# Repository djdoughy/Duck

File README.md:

# Duck
Pseudo Sidechain Compressor
Based on Modular for the Masses "OK BOOMER" schematic

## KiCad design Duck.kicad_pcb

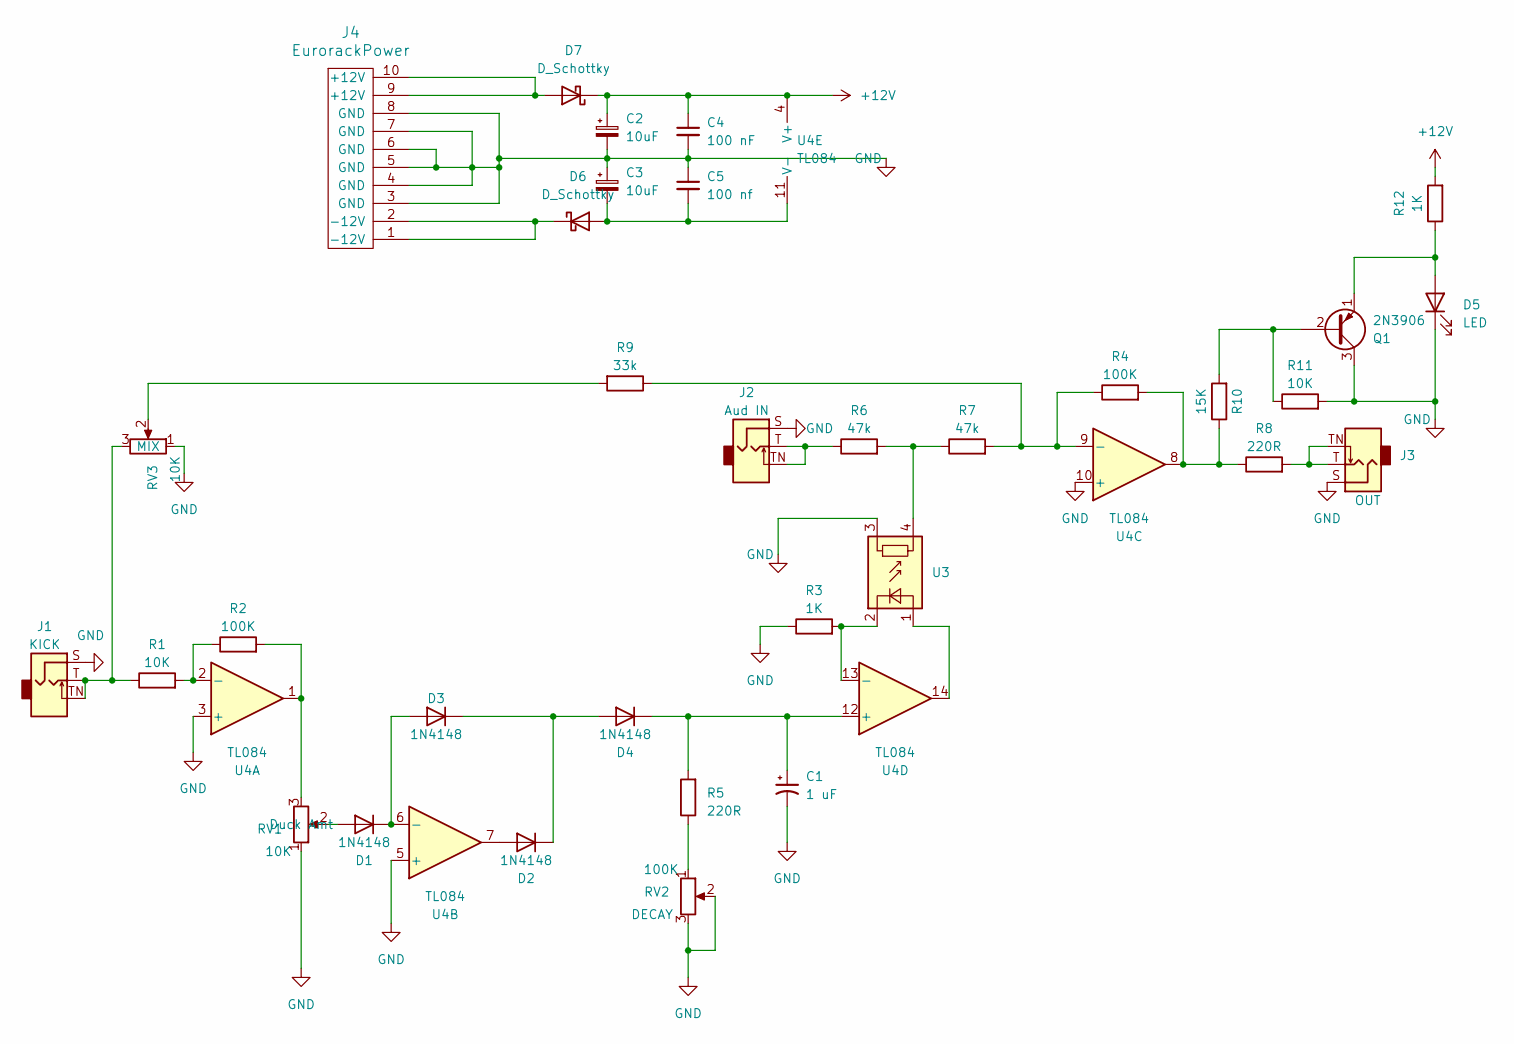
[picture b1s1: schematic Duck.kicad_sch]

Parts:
C1: 1 uF; CP_Radial_D5.0mm_P2.50mm
C2, C3: 10uF; CP_Radial_D5.0mm_P2.50mm
C4: 100 nF; C_Disc_D3.0mm_W2.0mm_P2.50mm
C5: 100 nf; C_Disc_D3.0mm_W2.0mm_P2.50mm
D1, D2, D3, D4: 1N4148; D_DO-35_SOD27_P7.62mm_Horizontal
D5: LED; LED3mm
D6, D7: D_Schottky; D_DO-35_SOD27_P7.62mm_Horizontal
J1: KICK; AudioJack_WQP518MA; MPN WQP-WQP518MA
J2: Aud IN; AudioJack_WQP518MA; MPN WQP-WQP518MA
J3: OUT; AudioJack_WQP518MA; MPN WQP-WQP518MA
J4: EurorackPower; IDC-Header_2x05_P2.54mm_Vertical
Q1: 2N3906; TO-92_HandSolder
R1: 10K; R_Axial_DIN0204_L3.6mm_D1.6mm_P7.62mm_Horizontal; Part Number RC0603FR-100RL; JLCPCB ID C21189
R2, R4, R10, R11, R12: 100K; R_Axial_DIN0204_L3.6mm_D1.6mm_P7.62mm_Horizontal; Part Number RC0603FR-100RL; JLCPCB ID C21189
R3: 1K; R_Axial_DIN0204_L3.6mm_D1.6mm_P7.62mm_Horizontal; Part Number RC0603FR-100RL; JLCPCB ID C21189
R5, R8: 220R; R_Axial_DIN0204_L3.6mm_D1.6mm_P7.62mm_Horizontal; Part Number RC0603FR-100RL; JLCPCB ID C21189
R6, R7: 47k; R_Axial_DIN0204_L3.6mm_D1.6mm_P7.62mm_Horizontal; Part Number RC0603FR-100RL; JLCPCB ID C21189
R9: 33k; R_Axial_DIN0204_L3.6mm_D1.6mm_P7.62mm_Horizontal; Part Number RC0603FR-100RL; JLCPCB ID C21189
RV1, RV3: 10K; Alpha9mmPot
RV2: 100K; Alpha9mmPot
U3: VTL5C; Vactrol
U4: TL084; DIP-14_W7.62mm

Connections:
+12V: C2.1, C4.1, D7.1 (K), R12.2, U4.4 (V+)
GND: C1.2, C2.2, C3.1, C4.2, C5.1, D5.1 (K), J1.S (Sleeve), J2.S (Sleeve), J3.S (Sleeve), J4.3 (GND), J4.4 (GND), J4.5 (GND), J4.6 (GND), J4.7 (GND), J4.8 (GND), Q1.3 (C), R3.1, R11.2, RV1.1, RV2.2, RV2.3, RV3.1, U3.3, U4.3 (+), U4.5 (+), U4.10 (+)
unnamed: D1.2 (A), RV1.2
unnamed: D1.1 (K), D3.2 (A), U4.6 (-)
unnamed: D2.2 (A), U4.7
unnamed: D2.1 (K), D3.1 (K), D4.2 (A)
unnamed: C1.1, D4.1 (K), R5.2, U4.12 (+)
unnamed: D5.2 (A), Q1.1 (E), R12.1
unnamed: C3.2, C5.2, D6.2 (A), U4.11 (V-)
unnamed: D6.1 (K), J4.1 (-12V), J4.2 (-12V)
unnamed: D7.2 (A), J4.9 (+12V), J4.10 (+12V)
unnamed: J1.T (Tip), J1.TN (Tip_normalize), R1.1, RV3.3
unnamed: J2.T (Tip), J2.TN (Tip_normalize), R6.1
unnamed: J3.T (Tip), J3.TN (Tip_normalize), R8.2
unnamed: Q1.2 (B), R10.2, R11.1
unnamed: R2.2, RV1.3, U4.1
unnamed: R5.1, RV2.1
unnamed: R6.2, R7.1, U3.4
unnamed: R9.2, RV3.2
unnamed: R4.2, R8.1, R10.1, U4.8
unnamed: U3.1 (+), U4.14
unnamed: R3.2, U3.2 (-), U4.13 (-)
unnamed: R1.2, R2.1, U4.2 (-)
unnamed: R4.1, R7.2, R9.1, U4.9 (-)

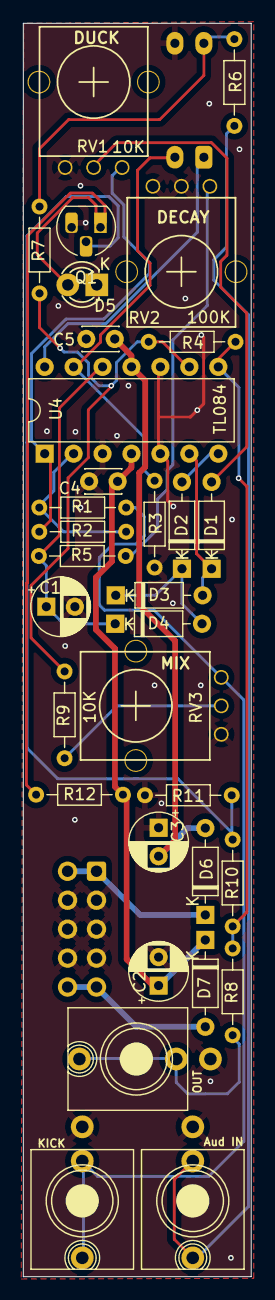
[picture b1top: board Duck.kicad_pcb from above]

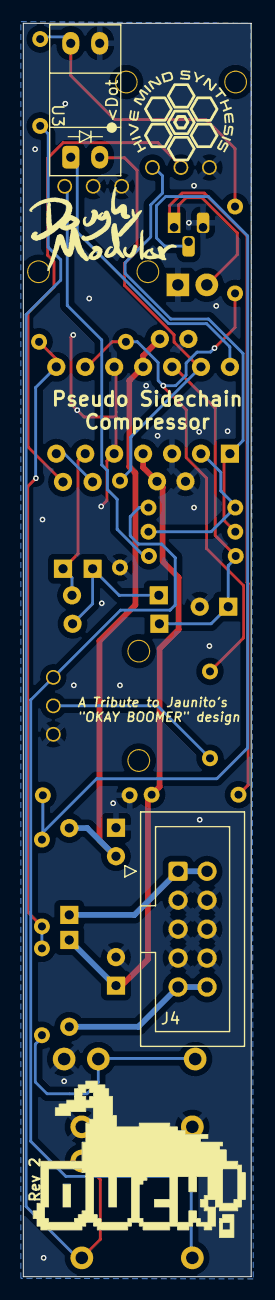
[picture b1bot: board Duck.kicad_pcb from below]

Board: 2 copper layers, 20.0 x 110.0 mm, 34 parts (2 on the bottom side), 24 nets.

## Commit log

2024-07-13 Init upload
    last changes were updates made for HMS production run
2024-07-13 Init upload
    Project File, updated 7-12 for HMS production
2024-07-13 Panel Init upload
    PCB panel for Duck
2024-07-13 Pot values added to schem and board
2024-07-13 Init upload of iBoM
2024-07-24 Delete ibom/DUCK-ibom-71224.html
    Improper values
2024-07-24 Updated values
    replacement for old ibom
